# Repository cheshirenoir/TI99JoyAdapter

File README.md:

# TI99JoyAdapter
A simple and small joystick adapter for the TI 99/4A

This is based on the common diode based adapter. Thanks to the original creators. 
A small signal diode should be used. Observe polarity! It changes halfway across to simplify routing. Something like an MM4148 should do.

CC BY SA

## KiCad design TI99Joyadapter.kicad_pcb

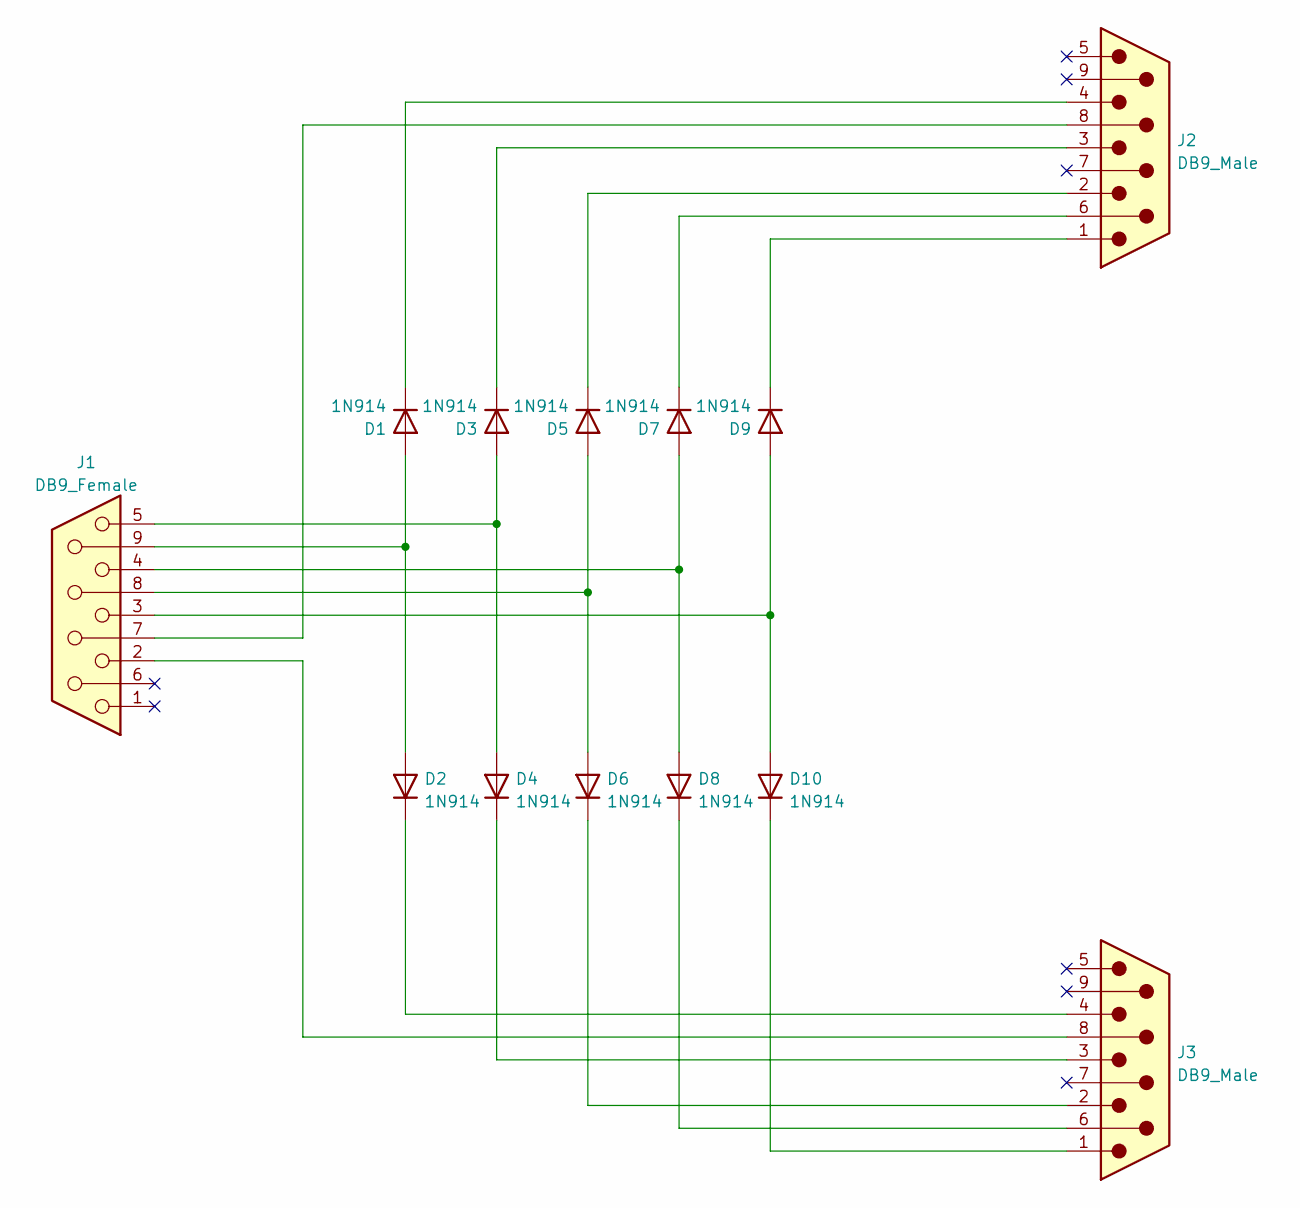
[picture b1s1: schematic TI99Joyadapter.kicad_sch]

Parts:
D1, D2, D3, D4, D5, D6, D7, D8, D9, D10: 1N914; D_SMA
J1: DB9_Female; DSUB-9_Female_Vertical_P2.77x2.84mm
J2, J3: DB9_Male; DSUB-9_Male_Vertical_P2.77x2.84mm

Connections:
unnamed: D1.1 (K), J2.4
unnamed: D1.2 (A), D2.2 (A), J1.9
unnamed: D2.1 (K), J3.4
unnamed: D3.1 (K), J2.3
unnamed: D3.2 (A), D4.2 (A), J1.5
unnamed: D4.1 (K), J3.3
unnamed: D5.1 (K), J2.2
unnamed: D5.2 (A), D6.2 (A), J1.8
unnamed: D6.1 (K), J3.2
unnamed: D7.1 (K), J2.6
unnamed: D7.2 (A), D8.2 (A), J1.4
unnamed: D8.1 (K), J3.6
unnamed: D9.1 (K), J2.1
unnamed: D10.1 (K), J3.1
unnamed: D9.2 (A), D10.2 (A), J1.3
unnamed: J1.2, J3.8
unnamed: J1.7, J2.8

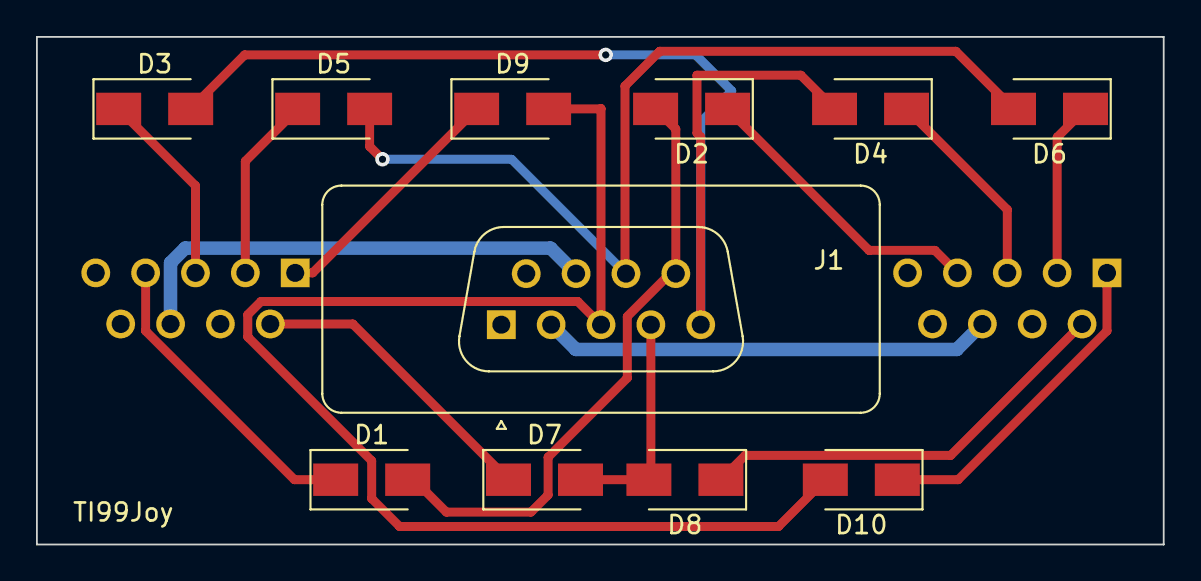
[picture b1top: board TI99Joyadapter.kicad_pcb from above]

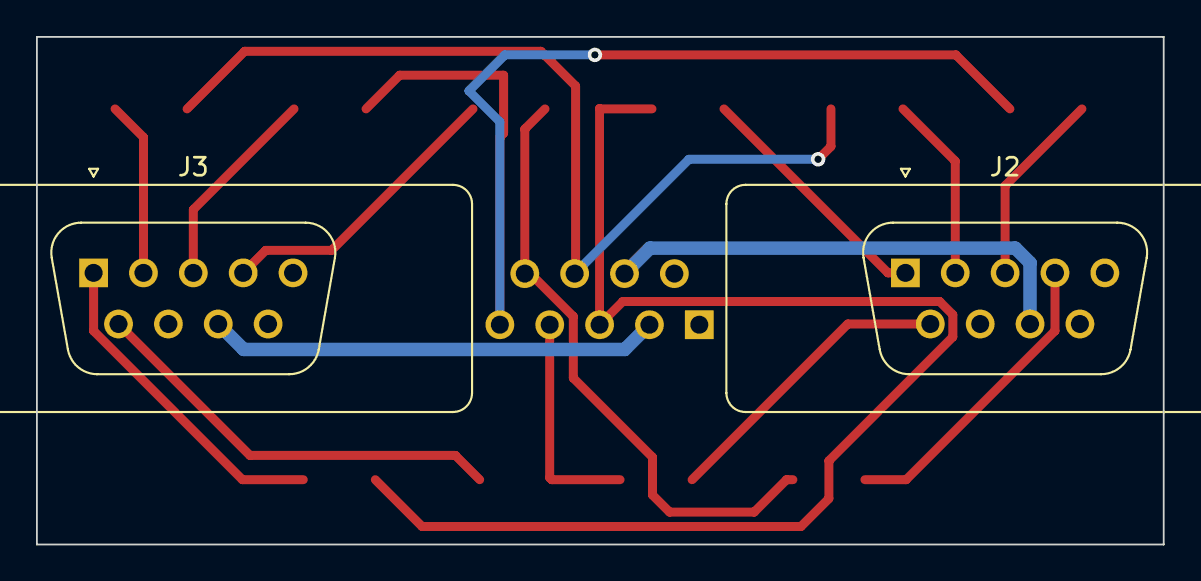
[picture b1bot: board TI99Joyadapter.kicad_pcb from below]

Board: 2 copper layers, 62.6 x 28.2 mm, 13 parts (2 on the bottom side), 17 nets.

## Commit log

2023-02-16 Add files via upload
    Initial upload
